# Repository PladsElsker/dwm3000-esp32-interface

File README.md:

# DWM3000 ESP32 Interface

A project for UWB ranging and BLE messaging using an ESP32-C3 and DWM3000.

## Projects

| Project | Purpose | Start here |
|---|---|---|
| [Firmware and host tools](dwm3000-firmware/README.md) | ESP32-C3 firmware, host protocol, Python client and protocol tests | Firmware README |
| [D3KM](d3km/README.md) | Tauri 2 desktop application for configuring and monitoring a node | D3KM README |
| [Hardware](dwm3000-board/README.md) | KiCad schematic, PCB and fabrication outputs | Hardware README |
| [d3kble Python API](d3kble-api/README.md) | Python API, automated tests, examples, and hardware integration tests for ESP32-C3 / DWM3000 nodes | d3kble API README |
| [Gazebo D3K simulator](simulation/gazebo/README.md) | Gazebo Harmonic system plugin emulating D3K UART, BLE messaging, and UWB ranging | Simulator README |

## System architecture

The ESP32-C3 runs the UWB node firmware and controls the DWM3000 radio. Host applications communicate with the node over USB CDC or UART1 using the same binary protocol. D3KM is one host; the Python client is another.

BLE is handled by the node firmware. D3KM sends BLE operations over the serial host protocol; it does not connect directly to the node over BLE.

The Gazebo simulator implements the same host-facing device boundary for virtual nodes. It exposes PTYs for the existing `d3kble` serial client and emulates BLE peer messaging and UWB ranging between simulated nodes. It is intended for integration tests and simulation, not physical RF validation.

The protocol reference is [dwm3000-firmware/PROTOCOL.md](dwm3000-firmware/PROTOCOL.md). Keep host implementations and the Gazebo simulator synchronized with it when changing firmware commands, events or payloads.

## Repository layout

- `dwm3000-firmware/` — firmware project documentation, host protocol, Python client and tests
- `dwm3000-firmware/UwbNode/` — ESP32-C3 Arduino firmware sketch and its embedded dependencies
- `d3km/` — Vue frontend and Tauri/Rust desktop backend
- `d3kble-api/` — Python host API, automated tests, examples, and real-device manual hardware tests
- `dwm3000-board/` — KiCad design and manufacturing files
- `simulation/gazebo/` — Gazebo Sim 8 plugin and SDF examples for simulated D3K nodes

## Development workflow

1. Review the hardware README and firmware pin map before wiring a board.
2. Build and flash the firmware to compatible nodes.
3. Connect a node through D3KM or the Python client.
4. Configure distinct node IDs and compatible UWB/BLE peer settings.
5. Validate serial communication, UWB ranging and BLE messaging independently.
6. Use the Gazebo simulator for host-protocol and application integration testing without physical nodes.

See each project README for its own setup and validation commands. Software tests do not establish hardware or RF performance.

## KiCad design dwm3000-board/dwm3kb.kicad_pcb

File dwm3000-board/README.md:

# DWM3000 Interface Board

KiCad hardware design for the DWM3000 and ESP32 interface project.

## Project files

- `dwm3kb.kicad_pro` — KiCad project
- `dwm3kb.kicad_sch` — schematic
- `dwm3kb.kicad_pcb` — PCB layout
- `dwm3000/` — local DWM3000 library assets
- Gerber, drill and job files — fabrication outputs from a design revision

The schematic title block identifies revision 0.2. Check the current schematic and PCB revision before using manufacturing files; generated outputs can become stale after design changes.

## Open and develop

1. Open `dwm3kb.kicad_pro` in KiCad.
2. Keep the local `dwm3000/` library assets available when opening or editing the design.
3. Review the schematic and run Electrical Rules Checker (ERC).
4. Review the PCB, refill copper zones and run Design Rules Checker (DRC).
5. After any layout change, regenerate Gerber and drill files from the current PCB.
6. Review the generated outputs and assembly requirements before sending them to a fabricator.

## Hardware integration

Check the firmware [pin map](../dwm3000-firmware/README.md#hardware-and-pin-map) against the actual schematic and assembled board. Pay particular attention to ESP32-C3 strapping pins, 3.3 V logic, power integrity, reset and wake signals, and the DWM3000 antenna/RF layout.

## Before fabrication

- Confirm schematic and PCB revisions match.
- Resolve or explicitly review ERC and DRC findings.
- Verify footprints, component values, connector orientation and assembly constraints.
- Regenerate fabrication outputs from the reviewed PCB.
- Review stack-up, board-house capabilities and RF layout requirements.

The presence of KiCad files and fabrication outputs does not imply electrical, RF, assembly or manufacturing qualification. Validate the assembled hardware before deployment.

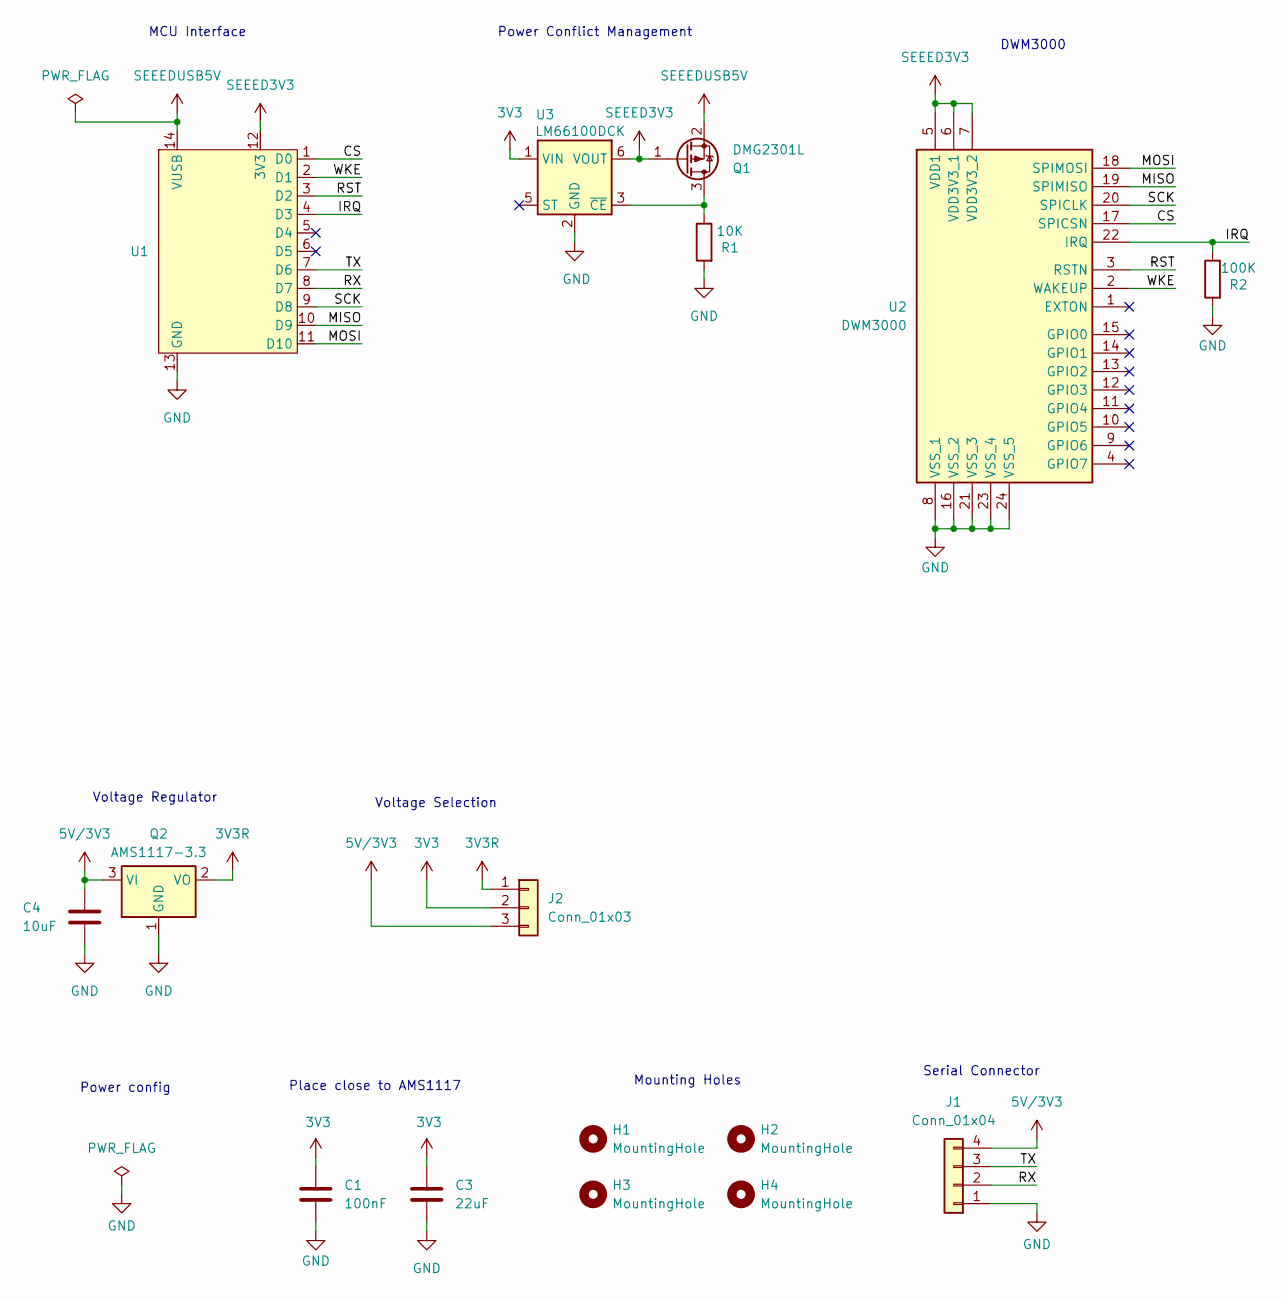
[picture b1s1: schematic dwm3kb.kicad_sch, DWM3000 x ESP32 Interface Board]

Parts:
C1: 100nF; C_0805_2012Metric
C3: 22uF; C_0805_2012Metric
C4: 10uF; C_0805_2012Metric
H1, H2, H3, H4: MountingHole; MountingHole_2.2mm_M2
J1: Conn_01x04; PinHeader_1x04_P2.54mm_Vertical
J2: Conn_01x03; SolderJumper-3_P2.0mm_Open_TrianglePad1.0x1.5mm
Q1: DMG2301L; SOT-23
Q2: AMS1117-3.3; SOT-223-3_TabPin2
R1: 10K; C_0805_2012Metric
R2: 100K; C_0805_2012Metric
U1: MCU_Seeed_ESP32C3
U2: DWM3000; DWM1000; Manufacturer_Part_Number DWM3000; Mouser Part Number N/A
U3: LM66100DCK; SOT-363_SC-70-6

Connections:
3V3: C1.1, C3.1, J2.2, U3.1 (VIN)
3V3R: J2.1, Q2.2 (VO)
5V/3V3: C4.1, J1.4, J2.3, Q2.3 (VI)
/CS: U1.1 (D0), U2.17 (SPICSN)
/IRQ: R2.1, U1.4 (D3), U2.22 (IRQ)
/MISO: U1.10 (D9), U2.19 (SPIMISO)
/MOSI: U1.11 (D10), U2.18 (SPIMOSI)
/RST: U1.3 (D2), U2.3 (RSTN)
/RX: J1.2, U1.8 (D7)
/SCK: U1.9 (D8), U2.20 (SPICLK)
/TX: J1.3, U1.7 (D6)
/WKE: U1.2 (D1), U2.2 (WAKEUP)
GND: C1.2, C3.2, C4.2, J1.1, Q2.1 (GND), R1.2, R2.2, U1.13 (GND), U2.8 (VSS_1), U2.16 (VSS_2), U2.21 (VSS_3), U2.23 (VSS_4), U2.24 (VSS_5), U3.2 (GND)
unnamed: Q1.3 (D), R1.1, U3.3 (~CE)
SEEED3V3: Q1.1 (G), U1.12 (3V3), U2.5 (VDD1), U2.6 (VDD3V3_1), U2.7 (VDD3V3_2), U3.6 (VOUT)
SEEEDUSB5V: Q1.2 (S), U1.14 (VUSB)

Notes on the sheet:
Voltage Regulator
Serial Connector
MCU Interface
Power Conflict Management
Voltage Selection
Place close to AMS1117
DWM3000
Mounting Holes
Power config

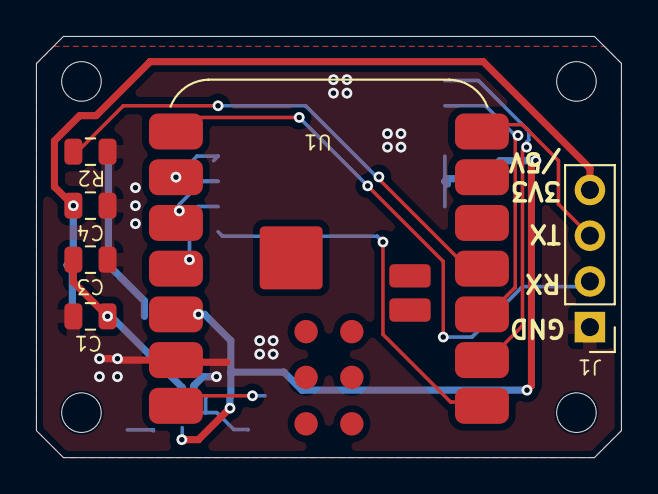
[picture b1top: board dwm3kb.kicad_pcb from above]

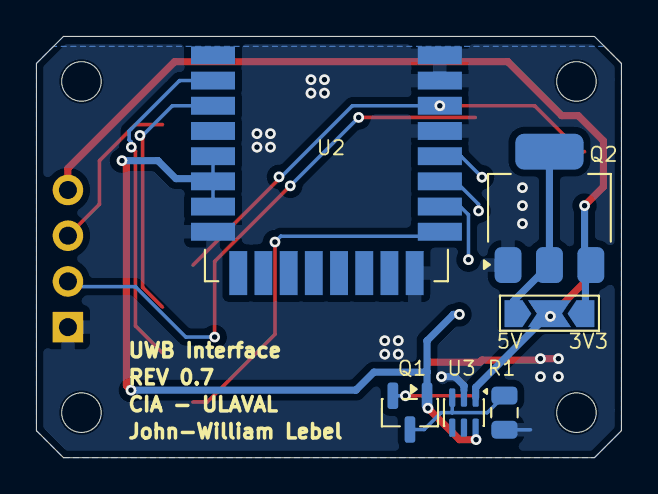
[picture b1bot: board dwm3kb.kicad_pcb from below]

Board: 2 copper layers, 32.5 x 23.4 mm, 16 parts (6 on the bottom side), 16 nets.
